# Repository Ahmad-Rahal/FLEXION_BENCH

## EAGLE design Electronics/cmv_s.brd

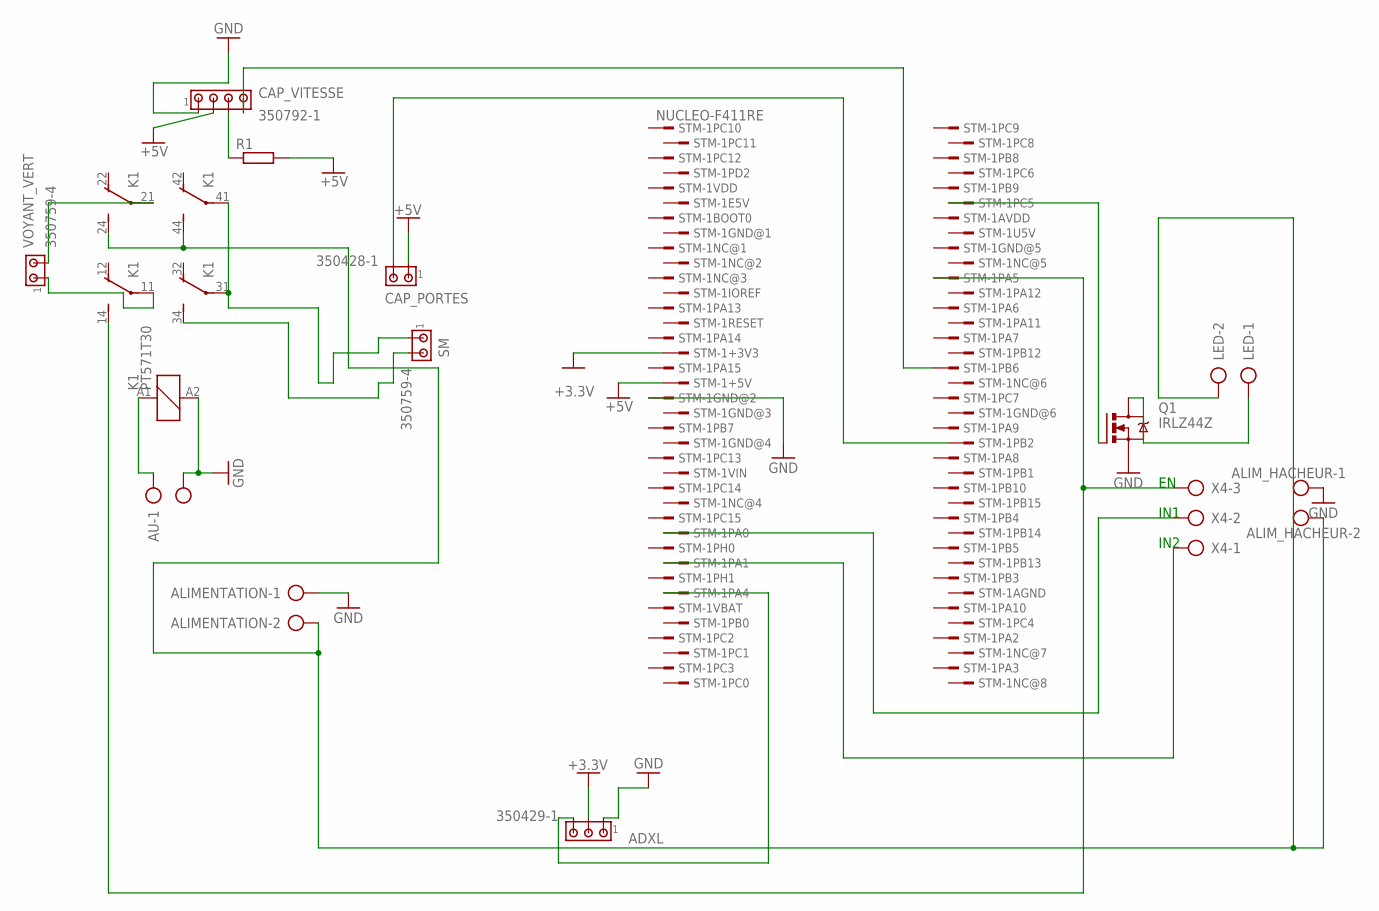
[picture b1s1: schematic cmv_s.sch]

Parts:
ADXL: 350429-1
ALIMENTATION: AK300/2
ALIM_HACHEUR: AK300/2
AU: AK300/2
CAP_PORTES: 350428-1
CAP_VITESSE: 350792-1
K1: PT571T30; PT-4
LED: AK300/2
Q1: IRLZ44Z; TO220BH
R1: R-EU_0204/7; 0204/7
SM: 350759-4
STM-1: NUCLEO-F411RE; CONN_STM32_NUCLEO
VOYANT_VERT: 350759-4
X4: AK300/3

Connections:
+3.3V: ADXL.2, STM-1.16
+5V: CAP_PORTES.1, CAP_VITESSE.2, R1.2, STM-1.18
GND: ADXL.1, ALIMENTATION.1, ALIM_HACHEUR.1, AU.2, CAP_VITESSE.1, K1.A2 (2), Q1.S, STM-1.19
unnamed: AU.1, K1.A1 (1)
unnamed: K1.34 (S), SM.2
unnamed: K1.11, VOYANT_VERT.1
unnamed: LED.1, Q1.D
unnamed: CAP_VITESSE.3, R1.1
unnamed: K1.21, VOYANT_VERT.2
unnamed: CAP_PORTES.2, STM-1.60
unnamed: K1.31, K1.41, SM.1
unnamed: CAP_VITESSE.4, STM-1.55
unnamed: ADXL.3, STM-1.32
unnamed: Q1.G, STM-1.44
unnamed: ALIMENTATION.2, ALIM_HACHEUR.2, K1.24 (S), K1.44 (S), LED.2
unnamed: K1.14 (S), STM-1.49, X4.3
unnamed: STM-1.28, X4.2
unnamed: STM-1.30, X4.1

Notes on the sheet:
IN1
IN2

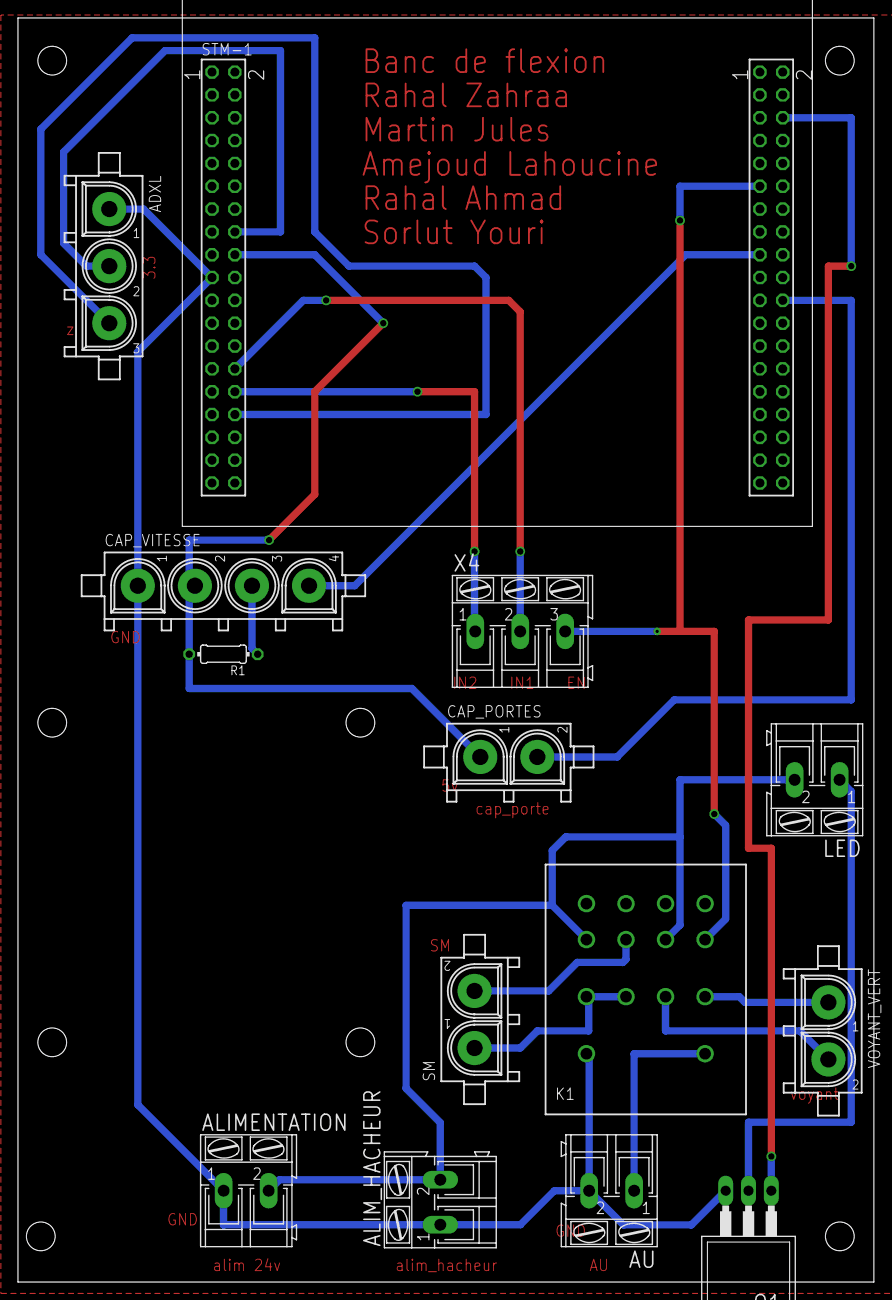
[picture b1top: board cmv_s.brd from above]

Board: 2 copper layers, 95.2 x 140.6 mm, 14 parts (0 on the bottom side), 18 nets.

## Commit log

2024-04-05 Project Code
2026-01-29 Initial
